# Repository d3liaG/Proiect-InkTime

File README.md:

# Proiect-InkTime
Design for a minimalist smartwatch optimized for month-class battery life and sunlight readability.

## Block Diagram

## Bill of Materials

| Component / Module | Qty | Purchase Link (JLC Parts) | Datasheet |
| :--- | :---: | :--- | :--- |
| **nRF52840 SoC** (Bluetooth MCU) | 1 | [JLC C190794](https://jlcpcb.com/partdetail/C190794) | [Download](https://files.seeedstudio.com/wiki/XIAO-BLE/Nano_BLE_MCU-nRF52840_PS_v1.1.pdf) |
| **BQ25180YBGR** (LiPo Charger) | 1 | [LCSC BQ25180](https://www.lcsc.com/search?q=BQ25180) | [Download](https://www.ti.com/lit/ds/symlink/bq25180.pdf) |
| **MAX17048G+T10** (Fuel Gauge) | 1 | [JLC C2682616](https://jlcpcb.com/partdetail/MaximIntegrated-MAX17048GT10/C2682616) | [Download](https://datasheets.maximintegrated.com/en/ds/MAX17048-MAX17049.pdf) |
| **RT6160AWSC** (Buck-Boost) | 1 | [JLC C7065276](https://jlcpcb.com/partdetail/C7065276) | [Download](https://www.richtek.com/assets/product_file/RT6160A/DS6160A-02.pdf) |
| **BMA423** (Accelerometer/IMU) | 1 | [Mouser BMA423](https://www.mouser.ro/ProductDetail/Bosch-Sensortec/BMA423) | [Download](https://www.bosch-sensortec.com/media/boschsensortec/downloads/datasheets/bst-bma423-ds000.pdf) |
| **DRV2605YZFR** (Haptic Driver) | 1 | [JLC C81079](https://jlcpcb.com/partdetail/C81079) | [Download](https://www.ti.com/lit/ds/symlink/drv2605.pdf) |
| **USBLC6-2SC6** (ESD Protection) | 1 | [JLC C2827654](https://jlcpcb.com/partdetail/TECHPUBLIC-USBLC62SC6/C2827654) | [Download](https://www.st.com/resource/en/datasheet/usblc6-2.pdf) |
| **KH-TYPE-C-16P** (USB-C Connector) | 1 | [JLC C709357](https://jlcpcb.com/partdetail/KH-TYPE-C-16P/C709357) | [Download](https://datasheet.lcsc.com/lcsc/2112221830_Shenzhen-Kinghelm-Elec-KH-TYPE-C-16P_C709357.pdf) |
| **FTC252012SR47MB** (0.47uH Inductor) | 1 | [JLC C5832368](https://jlcpcb.com/partdetail/6763488-FTC252012SR47MBCA/C5832368) | [Download](https://product.tdk.com/system/files/dam/doc/product/inductor/inductor/smd/catalog/inductor_commercial_power_mlp2016_en.pdf) |
| **2450AT18B100E** (Chip Antenna) | 1 | [JLC C11022](https://jlcpcb.com/partdetail/Johanson-Technology-2450AT18B100E/C11022) | [Download](https://www.johansontechnology.com/datasheets/2450AT18B100.pdf) |
| **EVP-AKE31A** (Tactile Buttons) | 3 | [Panasonic EVP-AKE31A](https://www.mouser.ro/ProductDetail/Panasonic/EVP-AKE31A) | [Download](https://industrial.panasonic.com/cdbs/www-data/pdf/ATV0000/ATV0000CE28.pdf) |
| **503480-2400** (E-Paper Connector) | 1 | [Molex 503480-2400](https://www.mouser.ro/ProductDetail/Molex/503480-2400) | [Download](https://www.molex.com/pdm_docs/sd/5034802400_sd.pdf) |
| **MBR0530** (Schottky Diode) | 3 | [JLC C475718](https://jlcpcb.com/partdetail/C475718) | [Download](https://www.onsemi.com/pdf/datasheet/mbr0530t1-d.pdf) |

## Hardware Functionality Overview
* Core MCU: Powered by the nRF52840 SoC, an ARM Cortex-M4F processor supporting Bluetooth LE and ultra-low power operation.
* Display Interface: Features an E-Paper Display connected via a 24-pin FPC connector (503480-2400). It uses a specialized E-Paper Drive Circuit for high-voltage pulse generation.
* Motion Sensing: Includes a BMA421 3-axis accelerometer (IMU) for step counting and gesture detection, connected via I2C.
* Tactile Feedback: Integrated DRV2605YZFR haptic driver to provide vibration alerts and tactile user interaction.
* Power Management:
  * LiPo Charging: Managed by the BQ25180YBGR IC for safe battery charging via USB-C.
Battery Gauging: Uses the MAX17048G+T10 fuel gauge to accurately monitor battery state-of-charge.

  * Voltage Regulation: An RT6160AWSC DC/DC buck-boost converter provides a stable 3.3V system rail from the fluctuating battery voltage.
* User Interface: Three tactile buttons for navigation: SW_UP, SW_ENT, and SW_DN.
* Communication & Debug:
   * Antenna: 2.4GHz ceramic chip antenna (2450AT18B100E) for Bluetooth connectivity.
   * SWD Interface: TC2030-IDC connector for programming and debugging the nRF52840.

## nRF52840 Detailed Pin Mapping
The pins are assigned to optimize low-power peripheral management and shared communication buses:

* I2C Bus (Shared):
P0.26 (SDA) & P0.27 (SCL): Shared bus for the IMU (BMA421), Fuel Gauge (MAX17048), Haptic Driver (DRV2605), and LiPo Charger (BQ25180).

* Navigation Buttons:
P1.04: Assigned to SW_UP.
P1.02: Assigned to SW_ENT.
P1.06: Assigned to SW_DN.

* E-Paper Display Control:
SPI Interface: Dedicated pins for MOSI, SCK, and CS for fast display updates.
P0.11 / P0.12: Control lines for display Reset, Busy, and Data/Command (D/C) selection.

* Power Control:
P0.14: Used as an enable signal (TIC_EN) for peripheral power management.

* Debug/Programming:
SWDIO / SWCLK: Dedicated hardware pins for Serial Wire Debug.

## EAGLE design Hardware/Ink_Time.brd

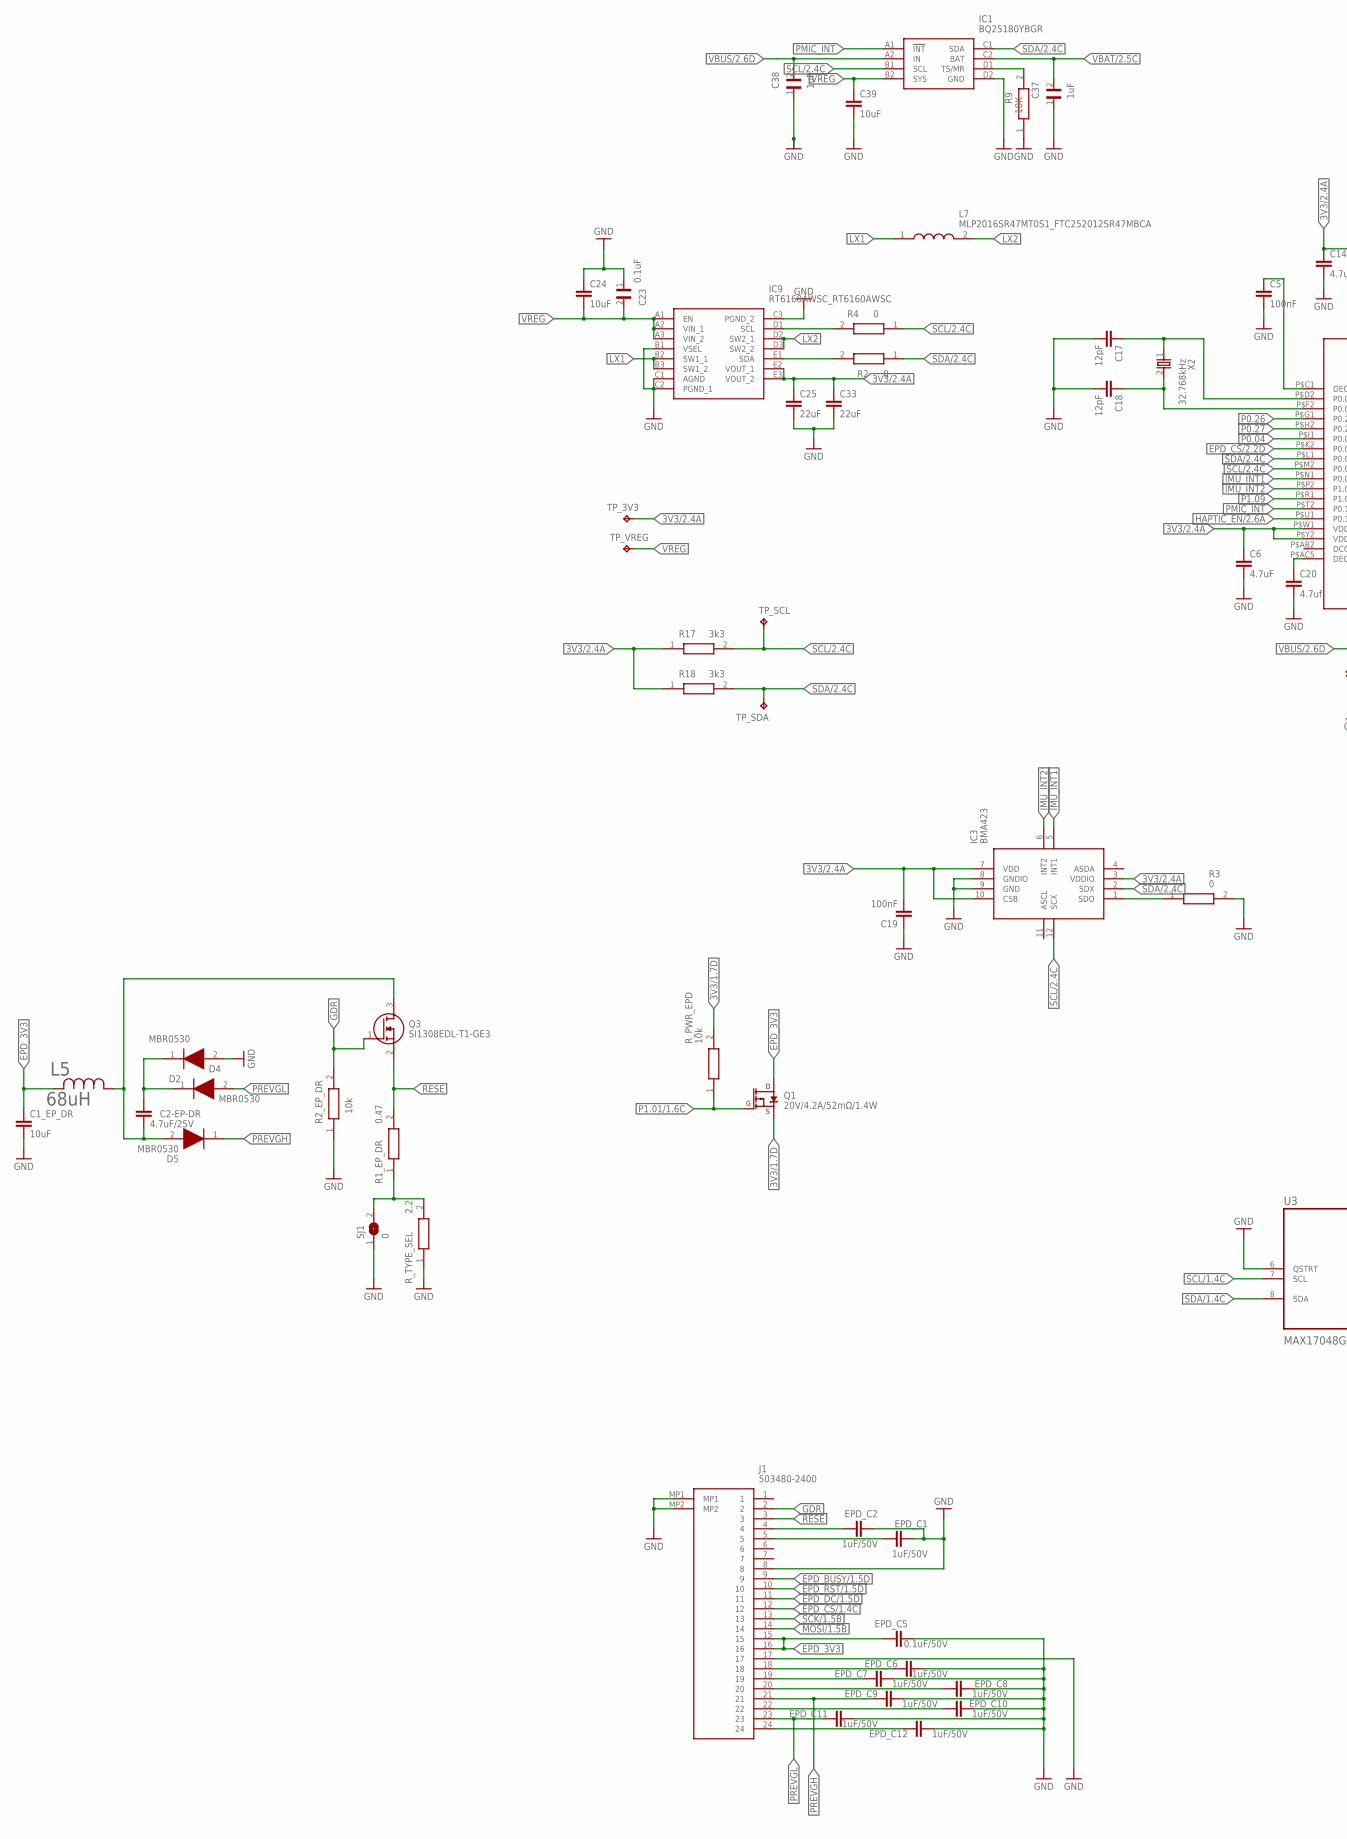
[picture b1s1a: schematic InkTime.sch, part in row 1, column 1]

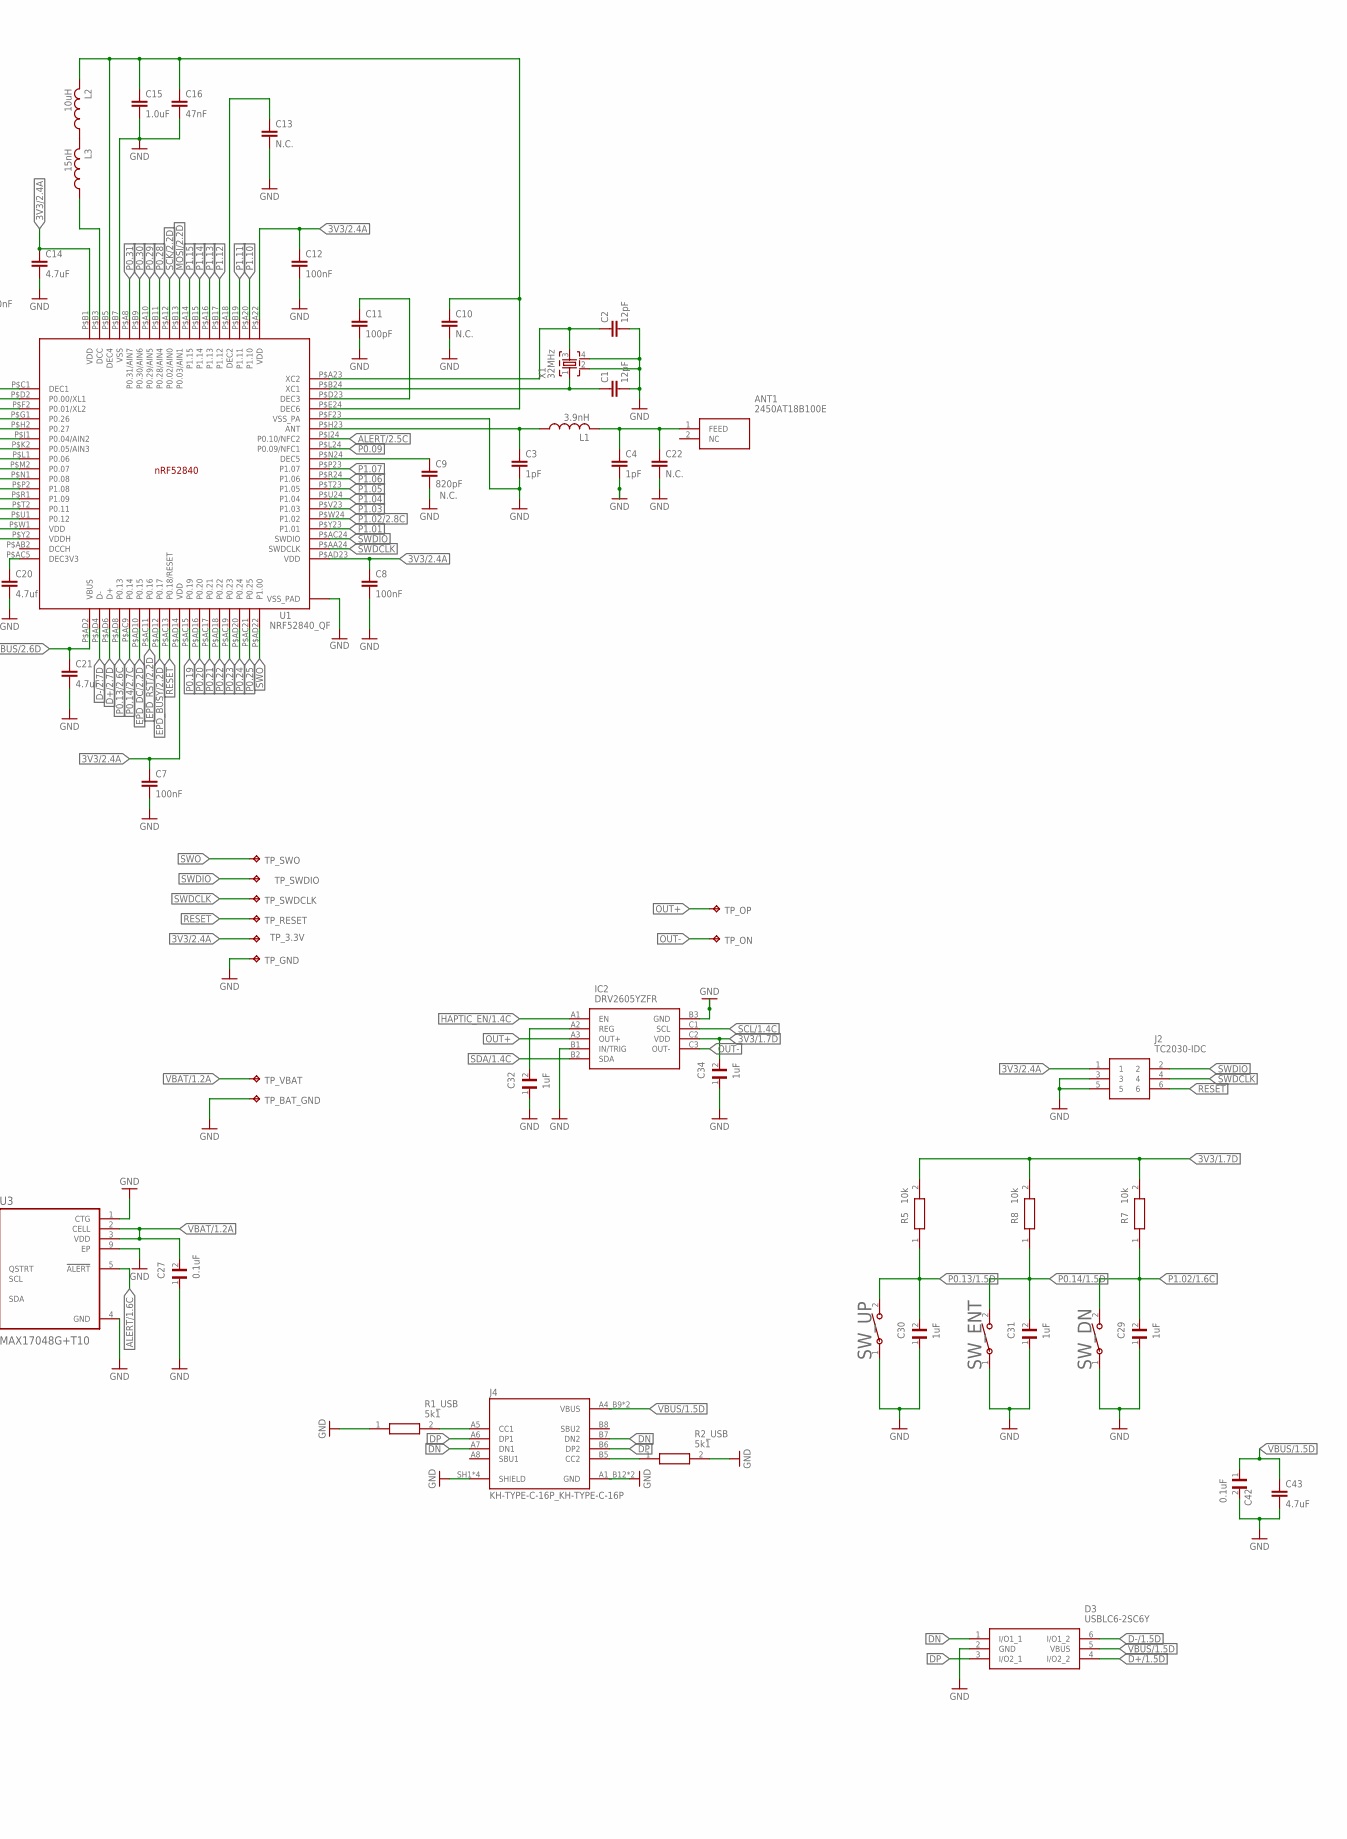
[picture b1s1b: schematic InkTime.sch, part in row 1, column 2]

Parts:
ANT1: 2450AT18B100E; 2450AT18B100E_ANTC3216X140N
C1, C2, C17, C18: 12pF; NORDIC_NRF_3_RESC0201_L
C1_EP_DR, C24, C39: 10uF; NORDIC_NRF_3_RESC0402_L
C2-EP-DR: 4.7uF/25V; NORDIC_NRF_3_RESC0603_L
C3, C4: 1pF; NORDIC_NRF_3_RESC0201_L
C5, C7, C8, C12, C19: 100nF; NORDIC_NRF_3_RESC0201_L
C6, C14, C21, C43: 4.7uF; NORDIC_NRF_3_RESC0402_L
C9: 820pF; NORDIC_NRF_3_RESC0201_L
C10, C13, C22: N.C.; NORDIC_NRF_3_RESC0402_L
C11: 100pF; NORDIC_NRF_3_RESC0201_L
C15: 1.0uF; NORDIC_NRF_3_RESC0402_L
C16: 47nF; NORDIC_NRF_3_RESC0201_L
C20: 4.7uf; NORDIC_NRF_3_RESC0201_L
C23, C27, C42: 0.1uF; GRM011R60J152KE01L_2_CAPC0201X13N
C25, C33: 22uF; NORDIC_NRF_3_RESC0402_L
C29, C30, C31, C32, C34, C37, C38: 1uF; GRM011R60J152KE01L_2_CAPC0201X13N
D2, D4, D5: MBR0530; ESP32_C6_LIBRARY_5_SOD3716X135N
D3: USBLC6-2SC6Y; ESP32_C6_LIBRARY_3_SOT95P280X145-6N
EPD_C1, EPD_C2, EPD_C6, EPD_C7, EPD_C8, EPD_C9, EPD_C10, EPD_C11, EPD_C12: 1uF/50V; RESC0402_L
EPD_C5: 0.1uF/50V; RESC0402_L
IC1: BQ25180YBGR; BQ25180YBGR_BGA8C40P2X4_100X155X50
IC2: DRV2605YZFR; DRV2605YZFR_BGA9C50P3X3_144X144X62
IC3: BMA423; BMA423_BMA423
IC9: RT6160AWSC_RT6160AWSC; RT6160AWSC_BGA15C40P3X5_140X230X60
J1: 503480-2400; 503480-2400_5034802400
J2: TC2030-IDC; TC2030-IDC_TC2030IDC
J4: KH-TYPE-C-16P_KH-TYPE-C-16P; KH-TYPE-C-16P_KINGHELM_KH-TYPE-C-16P
L1: 3.9nH; NORDIC_NRF_2_RESC0402_L
L2: 10uH; NORDIC_NRF_2_RESC0603_L
L3: 15nH; NORDIC_NRF_2_RESC0402_L
L5: 68uH; ESP32_C6_LIBRARY_2_IND_4828-WE-TPC_WRE
L7: MLP2016SR47MT0S1_FTC252012SR47MBCA; MLP2016SR47MT0S1_INDC2016X100N
Q1: 20V/4.2A/52mΩ/1.4W; ESP32_C6_LIBRARY_4_ESP32_C6_LIBRARY_4_ESP32_C6_LIBRARY_4_ES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
Q3: SI1308EDL-T1-GE3; ESP32_C6_LIBRARY_6_SOT65P210X110-3N
R1_EP_DR: 0.47; ERA-1AEB3401C_0201
R1_USB, R2_USB: 5k1; ERA-1AEB3401C_0201
R2, R3, R4: 0; ERA-1AEB3401C_0201
R2_EP_DR, R5, R7, R8: 10k; ERA-1AEB3401C_0201
R9: 10K; CPF0201D7K68C1_0201
R17: 3k3; ERA-1AEB3401C_0201
R18: 3k3; CPF0201D7K68C1_0201
R_PWR_EPD: 10k; ERA-1AEB3401C_0201
R_TYPE_SEL: 2.2; ERA-1AEB3401C_0201
SJ1: 0; ESP32_C6_LIBRARY_7_JUMPER_SJ
SW_DN: 2025-10-22_07-23-44_LIBRARY_EVP-AKE31ASW_EVP-AKE3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; 2025-10-22_07-23-44_LIBRARY_SW_EVP-AKE31A_PAN
SW_ENT: 2025-10-22_07-23-44_LIBRARY_EVP-AKE31ASW_EVP-AKE3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; 2025-10-22_07-23-44_LIBRARY_SW_EVP-AKE31A_PAN
SW_UP: 2025-10-22_07-23-44_LIBRARY_EVP-AKE31ASW_EVP-AKE3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; 2025-10-22_07-23-44_LIBRARY_SW_EVP-AKE31A_PAN
TP_3.3V, TP_3V3: HECTOR_WATCH_1_TPTP20R; HECTOR_WATCH_1_TP20R
TP_BAT_GND: HECTOR_WATCH_1_TPTP20R; HECTOR_WATCH_1_TP20R
TP_GND: HECTOR_WATCH_1_TPTP20R; HECTOR_WATCH_1_TP20R
TP_ON: HECTOR_WATCH_1_TPTP20R; HECTOR_WATCH_1_TP20R
TP_OP: HECTOR_WATCH_1_TPTP20R; HECTOR_WATCH_1_TP20R
TP_RESET: HECTOR_WATCH_1_TPTP20R; HECTOR_WATCH_1_TP20R
TP_SCL: HECTOR_WATCH_1_TPTP20R; HECTOR_WATCH_1_TP20R
TP_SDA: HECTOR_WATCH_1_TPTP20R; HECTOR_WATCH_1_TP20R
TP_SWDCLK: HECTOR_WATCH_1_TPTP20R; HECTOR_WATCH_1_TP20R
TP_SWDIO: HECTOR_WATCH_1_TPTP20R; HECTOR_WATCH_1_TP20R
TP_SWO: HECTOR_WATCH_1_TPTP20R; HECTOR_WATCH_1_TP20R
TP_VBAT: HECTOR_WATCH_1_TPTP20R; HECTOR_WATCH_1_TP20R
TP_VREG: HECTOR_WATCH_1_TPTP20R; HECTOR_WATCH_1_TP20R
U1: NRF52840_QF; NORDIC_NRF_4_AQFN50P700X700X85_HS-74N
U3: MAX17048G+T10; ESP32_C6_LIBRARY_SON50P200X200X80-9N
X1: 32MHz; NORDIC_NRF_BT-XTAL_2016_N
X2: 32.768kHz; NORDIC_NRF_1_XTAL_3215_N

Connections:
3V3/1.7D: C34.2, IC2.C2 (VDD), Q1.2 (S), R5.2, R7.2, R8.2, R_PWR_EPD.2
3V3/2.4A: C6.1, C7.1, C8.1, C12.1, C14.1, C19.2, C25.1, C33.1, IC3.3 (VDDIO), IC3.7 (VDD), IC3.10 (CSB), IC9.E2 (VOUT_1), IC9.E3 (VOUT_2), J2.1, R17.1, R18.1, TP_3.3V.TP, TP_3V3.TP, U1.P$A22 (VDD), U1.P$AD14 (VDD), U1.P$AD23 (VDD), U1.P$B1 (VDD), U1.P$W1 (VDD), U1.P$Y2 (VDDH)
ALERT/1.6C: U3.5 (!ALERT)
ALERT/2.5C: U1.P$J24 (P0.10/NFC2)
D+/1.5D: D3.4 (I/O2_2)
D+/2.7D: U1.P$AD6 (D+)
D-/1.5D: D3.6 (I/O1_2)
D-/2.7D: U1.P$AD4 (D-)
DN: D3.1 (I/O1_1), J4.A7 (DN1), J4.B7 (DN2)
DP: D3.3 (I/O2_1), J4.A6 (DP1), J4.B6 (DP2)
EPD_3V3: C1_EP_DR.1, EPD_C5.1, J1.15, J1.16, L5.2, Q1.3 (D)
EPD_BUSY/1.5D: J1.9
EPD_BUSY/2.2D: U1.P$AD12 (P0.17)
EPD_CS/1.4C: J1.12
EPD_CS/2.2D: U1.P$K2 (P0.05/AIN3)
EPD_DC/1.5D: J1.11
EPD_DC/2.2D: U1.P$AD10 (P0.15)
EPD_RST/1.5D: J1.10
EPD_RST/2.2D: U1.P$AC11 (P0.16)
GDR: J1.2, Q3.1 (G), R2_EP_DR.2
GND: C1.2, C1_EP_DR.2, C2.2, C3.2, C4.2, C5.2, C6.2, C7.2, C8.2, C9.2, C10.2, C11.2, C12.2, C13.2, C14.2, C15.2, C16.2, C17.2, C18.2, C19.1, C20.2, C21.2, C22.2, C23.1, C24.1, C25.2, C27.1, C29.1, C30.1, C31.1, C32.1, C33.2, C34.1, C37.1, C38.1, C39.2, C42.2, C43.2, D3.2 (GND), D4.2 (A), EPD_C1.2, EPD_C2.2, EPD_C5.2, EPD_C6.2, EPD_C7.2, EPD_C8.2, EPD_C9.2, EPD_C10.2, EPD_C11.2, EPD_C12.2, IC1.D2 (GND), IC2.B1 (IN/TRIG), IC2.B3 (GND), IC3.8 (GNDIO), IC3.9 (GND), IC9.B1 (VSEL), IC9.C1 (AGND), IC9.C2 (PGND_1), IC9.C3 (PGND_2), J1.8, J1.17, J1.MP1, J1.MP2, J2.3, J2.5, J4.A1_B12 (GND), J4.A12_B1 (GND), J4.SH1 (SHIELD), J4.SH2 (SHIELD), J4.SH3 (SHIELD), J4.SH4 (SHIELD), R1_USB.1, R2_EP_DR.1, R2_USB.2, R3.2, R9.1, R_TYPE_SEL.1, SJ1.1, SW_DN.1, SW_ENT.1, SW_UP.1, TP_BAT_GND.TP, TP_GND.TP, U1.P$74 (VSS_PAD), U1.P$75 (VSS_PAD), U1.P$76 (VSS_PAD), U1.P$77 (VSS_PAD), U1.P$78 (VSS_PAD), U1.P$79 (VSS_PAD), U1.P$80 (VSS_PAD), U1.P$81 (VSS_PAD), U1.P$82 (VSS_PAD), U1.P$83 (VSS_PAD), U1.P$84 (VSS_PAD), U1.P$85 (VSS_PAD), U1.P$86 (VSS_PAD), U1.P$87 (VSS_PAD), U1.P$88 (VSS_PAD), U1.P$89 (VSS_PAD), U1.P$90 (VSS_PAD), U1.P$B7 (VSS), U1.P$F23 (VSS_PA), U3.1 (CTG), U3.4 (GND), U3.6 (QSTRT), U3.9 (EP), X1.2, X1.4
HAPTIC_EN/1.4C: IC2.A1 (EN)
HAPTIC_EN/2.6A: U1.P$U1 (P0.12)
IMU_INT1: IC3.5 (INT1), U1.P$N1 (P0.08)
IMU_INT2: IC3.6 (INT2), U1.P$P2 (P1.08)
LX1: IC9.B2 (SW1_1), IC9.B3 (SW1_2), L7.1
LX2: IC9.D2 (SW2_1), IC9.D3 (SW2_2), L7.2
MOSI/1.5B: J1.14
MOSI/2.2D: U1.P$B13 (P0.03/AIN1)
unnamed: C20.1, U1.P$AC5 (DEC3V3)
unnamed: C18.1, U1.P$F2 (P0.01/XL2), X2.2
unnamed: C5.1, U1.P$C1 (DEC1)
unnamed: C11.1, U1.P$D23 (DEC3)
unnamed: C2.1, U1.P$A23 (XC2), X1.3
unnamed: L2.1, L3.2
unnamed: L3.1, U1.P$B3 (DCC)
unnamed: IC3.1 (SDO), R3.1
unnamed: IC9.E1 (SDA), R2.2
unnamed: IC9.D1 (SCL), R4.2
unnamed: C17.1, U1.P$D2 (P0.00/XL1), X2.1
unnamed: IC1.D1 (TS/MR), R9.2
unnamed: C32.2, IC2.A2 (REG)
unnamed: J4.A5 (CC1), R1_USB.2
unnamed: J4.B5 (CC2), R2_USB.1
unnamed: EPD_C2.1, J1.4
unnamed: EPD_C1.1, J1.5
unnamed: EPD_C6.1, J1.18
unnamed: C13.1, U1.P$A18 (DEC2)
unnamed: EPD_C7.1, J1.19
unnamed: EPD_C8.1, J1.20
unnamed: EPD_C10.1, J1.22
unnamed: EPD_C12.1, J1.24
unnamed: C10.1, C15.1, C16.1, L2.2, U1.P$B5 (DEC4), U1.P$E24 (DEC6)
unnamed: C1.1, U1.P$B24 (XC1), X1.1
unnamed: R1_EP_DR.1, R_TYPE_SEL.2, SJ1.2
unnamed: C2-EP-DR.2, D5.2 (A), L5.1, Q3.3 (D)
unnamed: C2-EP-DR.1, D2.1 (K), D4.1 (K)
unnamed: C3.1, L1.1, U1.P$H23 (ANT)
unnamed: ANT1.1 (FEED), C4.1, C22.1, L1.2
unnamed: C9.1, U1.P$N24 (DEC5)
OUT+: IC2.A3 (OUT+), TP_OP.TP
OUT-: IC2.C3 (OUT-), TP_ON.TP
P0.04: U1.P$J1 (P0.04/AIN2)
P0.09: U1.P$L24 (P0.09/NFC1)
P0.13/1.5D: C30.2, R5.1, SW_UP.2
P0.13/2.6C: U1.P$AD8 (P0.13)
P0.14/1.5D: C31.2, R8.1, SW_ENT.2
P0.14/2.7C: U1.P$AC9 (P0.14)
P0.19: U1.P$AC15 (P0.19)
P0.20: U1.P$AD16 (P0.20)
P0.21: U1.P$AC17 (P0.21)
P0.22: U1.P$AD18 (P0.22)
P0.23: U1.P$AC19 (P0.23)
P0.24: U1.P$AD20 (P0.24)
P0.25: U1.P$AC21 (P0.25)
P0.26: U1.P$G1 (P0.26)
P0.27: U1.P$H2 (P0.27)
P0.28: U1.P$B11 (P0.28/AIN4)
P0.29: U1.P$A10 (P0.29/AIN5)
P0.30: U1.P$B9 (P0.30/AIN6)
P0.31: U1.P$A8 (P0.31/AIN7)
P1.01: U1.P$Y23 (P1.01)
P1.01/1.6C: Q1.1 (G), R_PWR_EPD.1
P1.02/1.6C: C29.2, R7.1, SW_DN.2
P1.02/2.8C: U1.P$W24 (P1.02)
P1.03: U1.P$V23 (P1.03)
P1.04: U1.P$U24 (P1.04)
P1.05: U1.P$T23 (P1.05)
P1.06: U1.P$R24 (P1.06)
P1.07: U1.P$P23 (P1.07)
P1.09: U1.P$R1 (P1.09)
P1.10: U1.P$A20 (P1.10)
P1.11: U1.P$B19 (P1.11)
P1.12: U1.P$B17 (P1.12)
P1.13: U1.P$A16 (P1.13)
P1.14: U1.P$B15 (P1.14)
P1.15: U1.P$A14 (P1.15)
PMIC_INT: IC1.A1 (!INT), U1.P$T2 (P0.11)
PREVGH: D5.1 (K), EPD_C9.1, J1.21
PREVGL: D2.2 (A), EPD_C11.1, J1.23
RESE: J1.3, Q3.2 (S), R1_EP_DR.2
RESET: J2.6, TP_RESET.TP, U1.P$AC13 (P0.18/RESET)
SCK/1.5B: J1.13
SCK/2.2D: U1.P$A12 (P0.02/AIN0)
SCL/1.4C: IC2.C1 (SCL), U3.7 (SCL)
SCL/2.4C: IC1.B1 (SCL), IC3.12 (SCX), R4.1, R17.2, TP_SCL.TP, U1.P$M2 (P0.07)
SDA/1.4C: IC2.B2 (SDA), U3.8 (SDA)
SDA/2.4C: IC1.C1 (SDA), IC3.2 (SDX), R2.1, R18.2, TP_SDA.TP, U1.P$L1 (P0.06)
SWDCLK: J2.4, TP_SWDCLK.TP, U1.P$AA24 (SWDCLK)
SWDIO: J2.2, TP_SWDIO.TP, U1.P$AC24 (SWDIO)
SWO: TP_SWO.TP, U1.P$AD22 (P1.00)
VBAT/1.2A: C27.2, TP_VBAT.TP, U3.2 (CELL), U3.3 (VDD)
VBAT/2.5C: C37.2, IC1.C2 (BAT)
VBUS/1.5D: C42.1, C43.1, D3.5 (VBUS), J4.A4_B9 (VBUS), J4.A9_B4 (VBUS)
VBUS/2.6D: C21.1, C38.2, IC1.A2 (IN), U1.P$AD2 (VBUS)
VREG: C23.2, C24.2, C39.1, IC1.B2 (SYS), IC9.A1 (EN), IC9.A2 (VIN_1), IC9.A3 (VIN_2), TP_VREG.TP

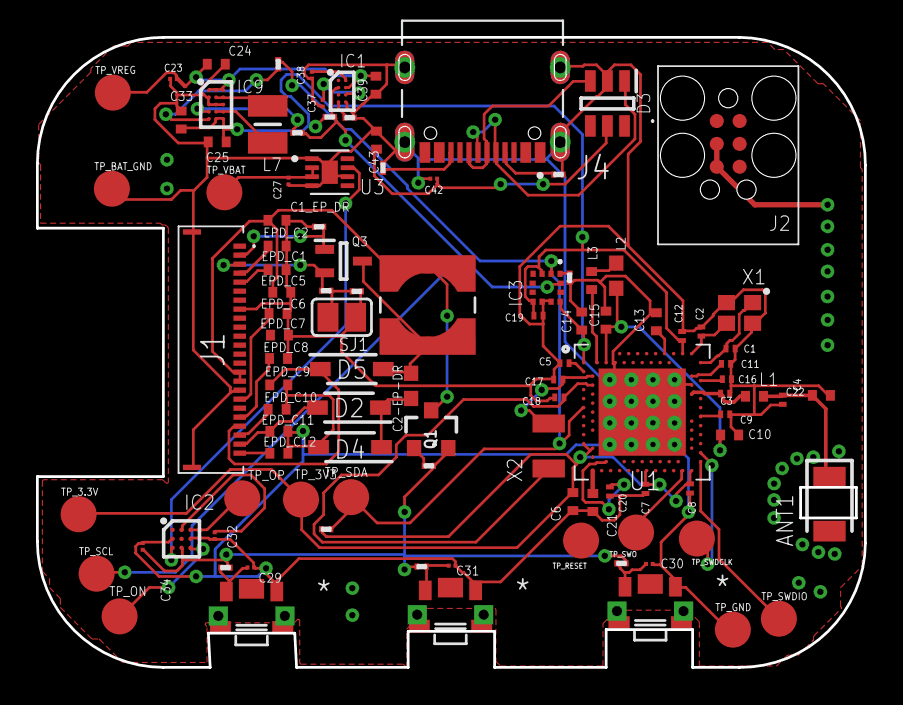
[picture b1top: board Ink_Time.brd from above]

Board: 4 copper layers, 46.0 x 35.0 mm, 105 parts (0 on the bottom side), 65 nets.

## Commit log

2026-04-17 schematic done, work in progress for pcb routing
2026-04-21 revised schematic and added pdf
2026-04-22 Added manufacturing files
2026-04-22 Completed Readme
2026-04-22 via stitching
2026-04-22 fitted pcb in the case

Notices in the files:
parts and their libraries:
InkTime_v5: COPYRIGHT: Copyright (C) 2025 Ultra Librarian. All rights reserved.
InkTime_v5: COPYRIGHT: Copyright (C) 2024 Ultra Librarian. All rights reserved.
